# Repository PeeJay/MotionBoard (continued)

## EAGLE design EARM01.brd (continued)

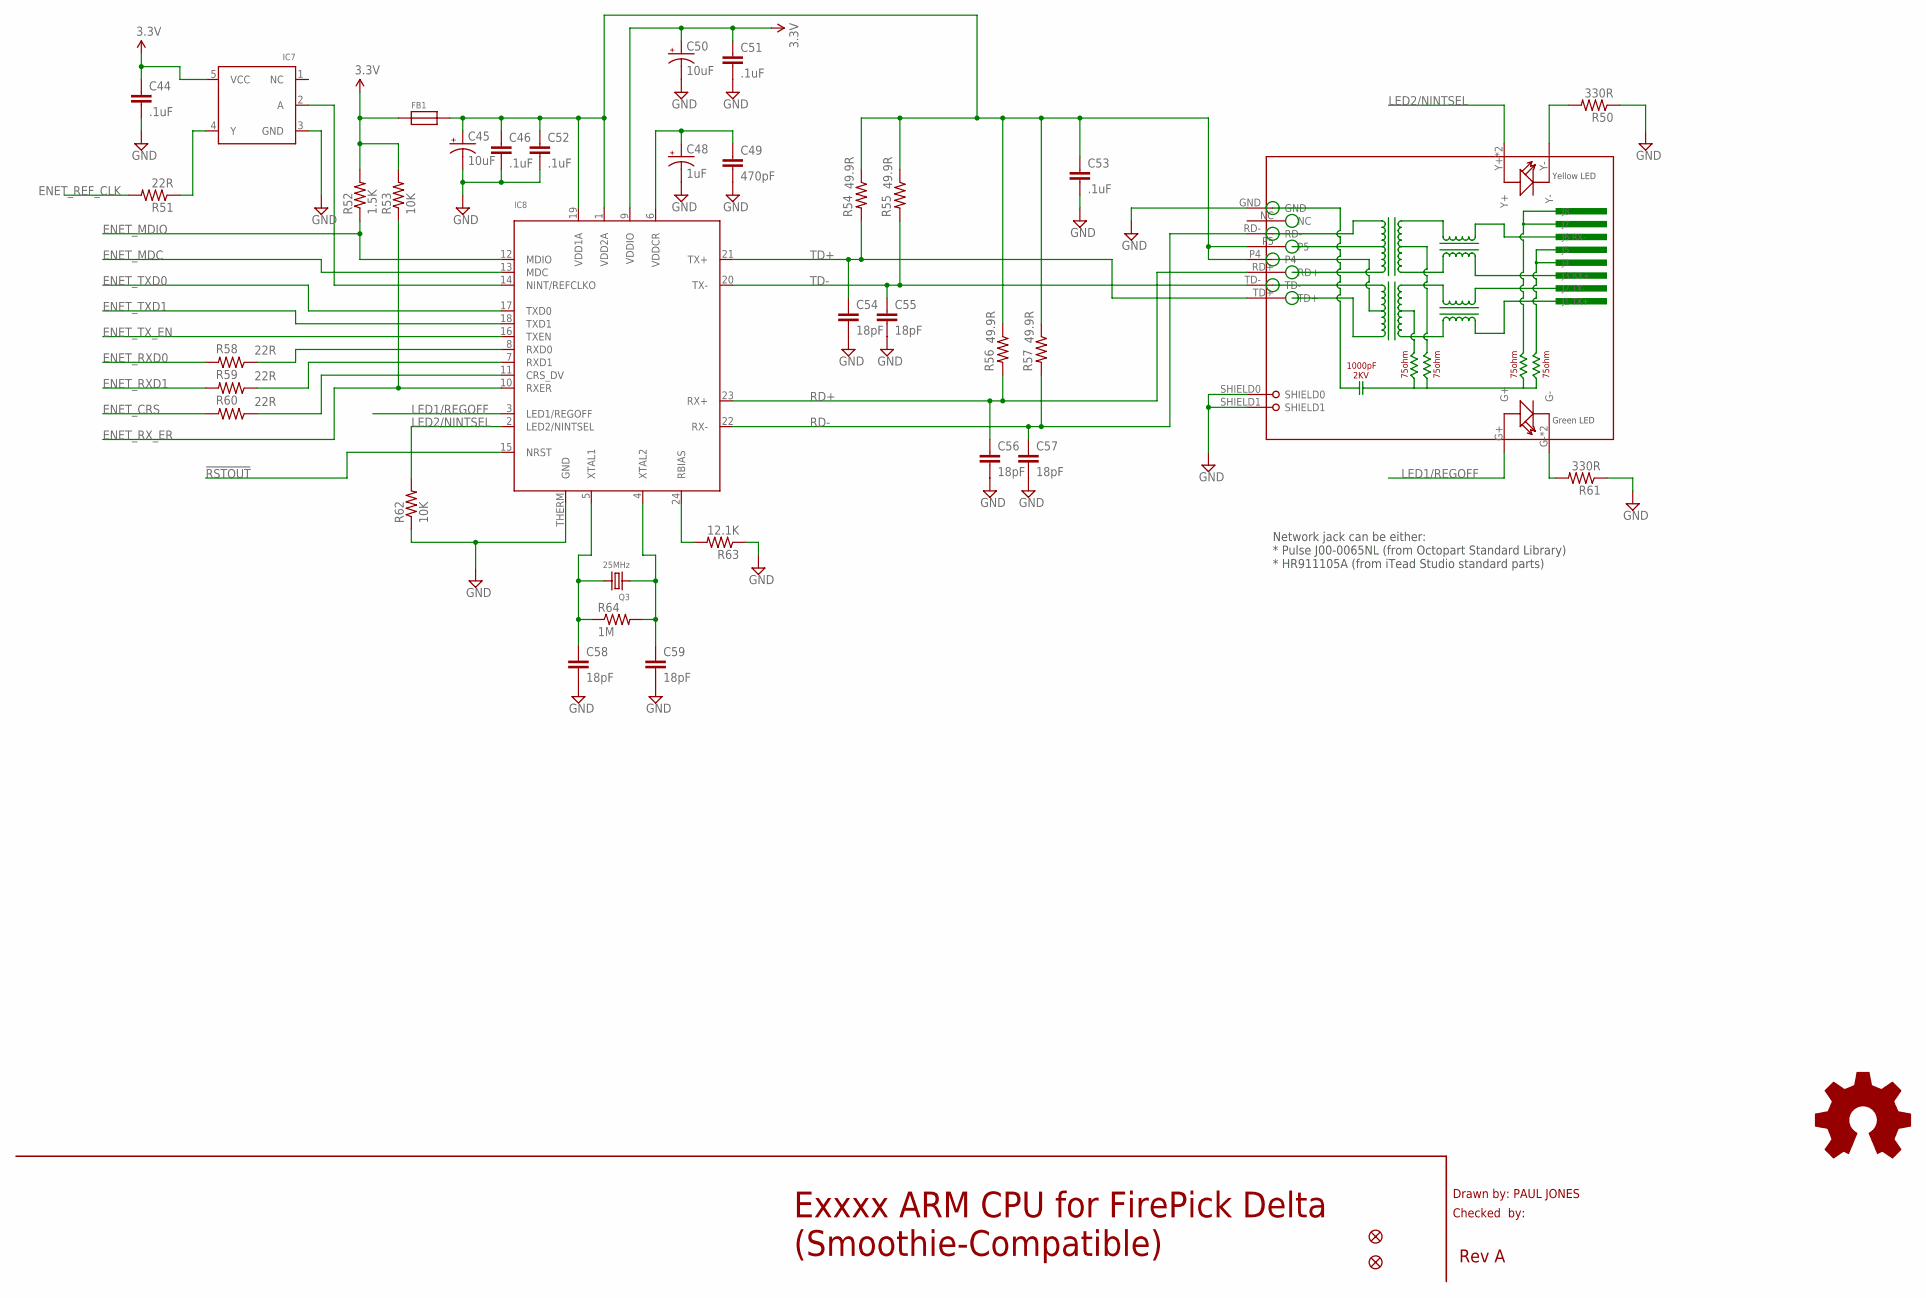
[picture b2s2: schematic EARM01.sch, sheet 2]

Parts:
C44, C46, C51, C52, C53: .1uF; C0603
C45, C50: 10uF; EIA3216
C48: 1uF; EIA3216
C49: 470pF; C0603K
C54, C55, C56, C57, C58, C59: 18pF; C0603
FB1: FERRITE; 0603
FID17, FID18: FIDUCIAL1X2; FIDUCIAL-1X2
IC7: 74LVC1G04; SOT23-5
IC8: LAN8720; QFN24_4MM
LOGO10: LOGO-OSHWSMALL; LOGO-OSHW-SMALL
Q3: 25MHz; CRYSTAL_3.2X2.5
R50, R61: 330R; R0603
R51, R58, R59, R60: 22R; R0603
R52: 1.5K; R0603
R53, R62: 10K; R0603
R54, R55, R56, R57: 49.9R; R0603
R63: 12.1K; R0603
R64: 1M; R0603
RJ1: HR911105A

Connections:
3.3V: C44.1, C50.A (+), C51.1, FB1.1, IC7.5 (VCC), IC8.9 (VDDIO), R52.2, R53.2; also elsewhere on the board
!RSTOUT: IC8.15 (NRST); also elsewhere on the board
ENET_CRS: R60.2; also elsewhere on the board
ENET_MDC: IC8.13 (MDC); also elsewhere on the board
ENET_MDIO: IC8.12 (MDIO), R52.1; also elsewhere on the board
ENET_REF_CLK: R51.2; also elsewhere on the board
ENET_RXD0: R58.2; also elsewhere on the board
ENET_RXD1: R59.2; also elsewhere on the board
ENET_RX_ER: IC8.10 (RXER), R53.1; also elsewhere on the board
ENET_TXD0: IC8.17 (TXD0); also elsewhere on the board
ENET_TXD1: IC8.18 (TXD1); also elsewhere on the board
ENET_TX_EN: IC8.16 (TXEN); also elsewhere on the board
GND: C44.2, C45.C (-), C46.2, C48.C (-), C49.2, C50.C (-), C51.2, C52.2, C53.2, C54.2, C55.2, C56.2, C57.2, C58.2, C59.2, IC7.3 (GND), IC8.THERM (GND), R50.1, R61.1, R62.1, R63.1, RJ1.GND, RJ1.SHIELD0, RJ1.SHIELD1; also elsewhere on the board
LED1/REGOFF: IC8.3 (LED1/REGOFF), RJ1.G+
LED2/NINTSEL: IC8.2 (LED2/NINTSEL), R62.2, RJ1.Y+, RJ1.Y++ (Y+)
unnamed: IC8.11 (CRS_DV), R60.1
unnamed: IC8.24 (RBIAS), R63.2
unnamed: C48.A (+), C49.1, IC8.6 (VDDCR)
unnamed: IC7.2 (A), IC8.14 (NINT/REFCLKO)
unnamed: R61.2, RJ1.G-, RJ1.G-- (G-)
unnamed: IC8.8 (RXD0), R58.1
unnamed: R50.2, RJ1.Y-
unnamed: IC8.7 (RXD1), R59.1
unnamed: C59.1, IC8.4 (XTAL2), Q3.1, R64.2
unnamed: C58.1, IC8.5 (XTAL1), Q3.2, R64.1
unnamed: IC7.4 (Y), R51.1
RD+: C56.1, IC8.23 (RX+), R56.2, RJ1.RD+
RD-: C57.1, IC8.22 (RX-), R57.2, RJ1.RD-
TD+: C54.1, IC8.21 (TX+), R54.2, RJ1.TD+
TD-: C55.1, IC8.20 (TX-), R55.2, RJ1.TD-
VDD: C45.A (+), C46.1, C52.1, C53.1, FB1.2, IC8.1 (VDD2A), IC8.19 (VDD1A), R54.1, R55.1, R56.1, R57.1, RJ1.P4, RJ1.P5

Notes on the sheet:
Drawn by: PAUL JONES
Checked by:
Rev A
Exxxx ARM CPU for FirePick Delta (Smoothie-Compatible)
Network jack can be either: * Pulse J00‑0065NL (from Octopart Standard Library) * HR911105A (from iTead Studio standard parts)

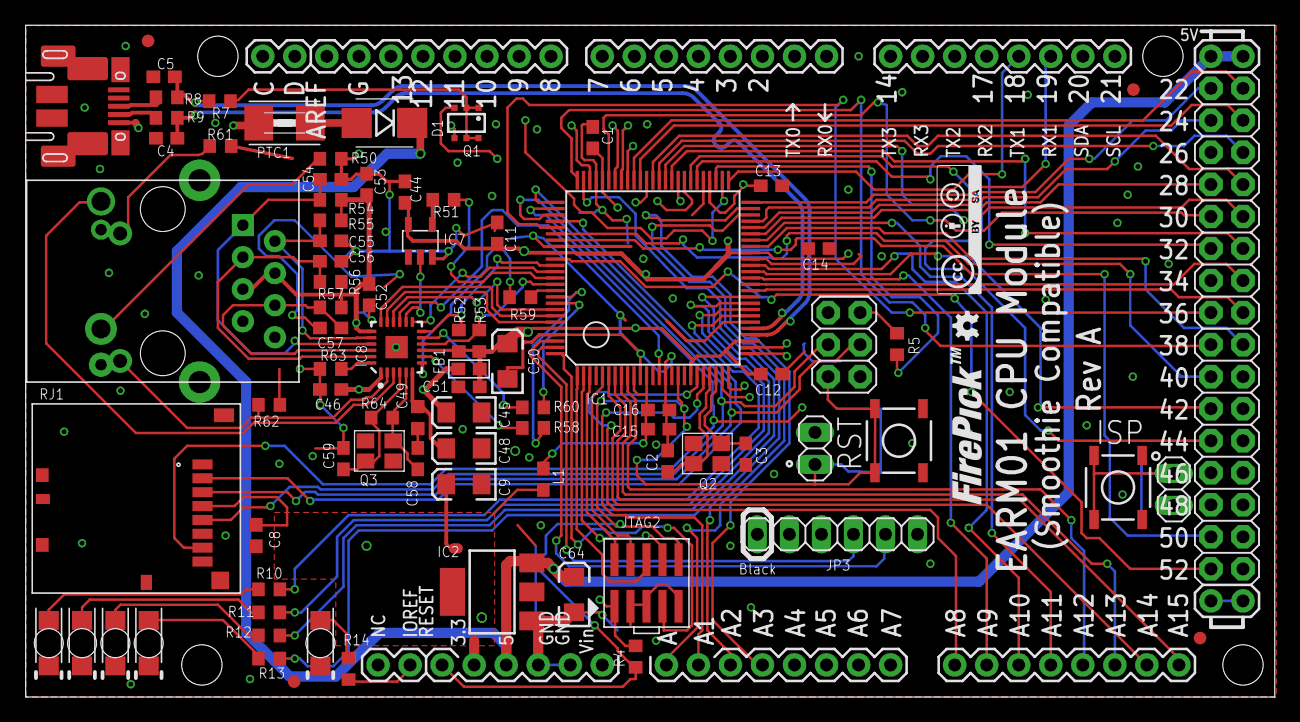
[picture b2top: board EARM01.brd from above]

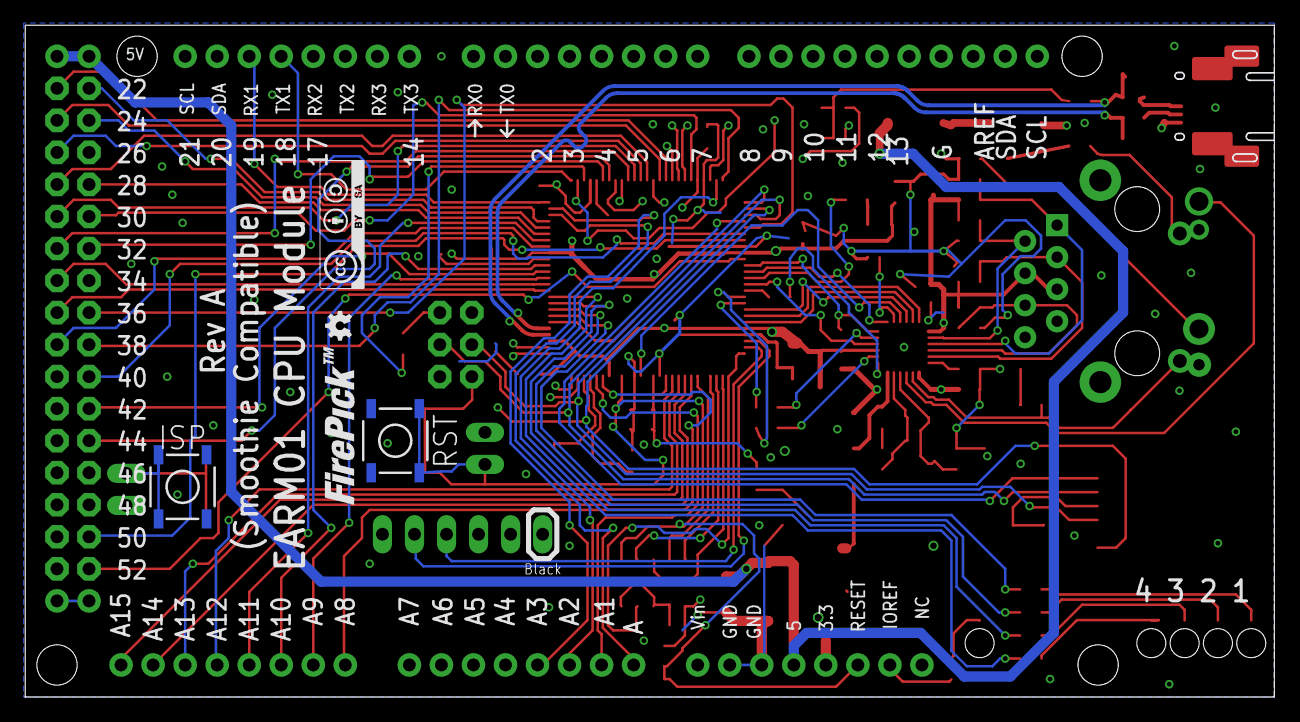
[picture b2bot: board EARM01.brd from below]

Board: 4 copper layers, 98.9 x 53.1 mm, 92 parts (5 on the bottom side), 111 nets.

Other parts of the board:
LOGO1: LOGO-FIREPICKMEDIUM; LOGO-FIREPICK-MEDIUM
LOGO2: LOGO-OSHWSMALL; LOGO-OSHW-SMALL
LOGO3: LOGO-CC-BY-SAMEDIUM; LOGO-CC-BY-SA-MEDIUM

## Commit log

2015-06-06 Add board files
2015-06-09 Update board files
2015-06-12 Cosmetic changes
    Add new name to schematic and rearrange page 1 so it all fits on the
    page
2015-06-28 Update with production files
    Also note a "whoopsie" where wire jumpers are required...
2015-09-29 Add rev C board
    * Fix misrouted Arduino pins
    * Replace obsolete Micro SD Card
    * Add analog input buffering + 5v voltage divider
    * Add solder jumpers to AREF and VIN
    * Add extra filtering to AREF and analog inputs
2016-01-11 Update component values
2016-01-11 Forgot to update resistor divider values
2020-12-12 Add PDFs
